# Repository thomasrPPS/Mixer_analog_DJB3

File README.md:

# Mixer_analog_DJB3

15 juin 2020 - 30 décembre 2020

Sommaire

Schema bloc, introduction
Tranche Phono/line
Autres éléments
PCB design
Montage
Démonstration
Sources

## Introduction

Voici le schéma du mixer V1 DJB3, pensé pour ressembler à un rotary mixer professionnel tel que la E&S DJR-400 ou la  Rane MP2015. 
Elle comprend 3 entrées Phono/Line pour tout type de signaux. De la platine vinyle aux drums machines et synthétiseurs. La première étape a été la modélisation 3d effectuée sur Blender
Chaque tranche est composée d’un equalizer 2 bandes grave/aigu sur les modèles de Baxandall.
Ensuite il y a un préamplificateur doté d’un switch selon la source entrante. Le coté phono se chargera d’appliquer la courbe RIAA et le gain est fixe (environ +40 dB à 20 Hz et +20 dB à 1 kHz). Le coté line sera doté d’un potentiomètre de gain à régler selon les besoins. 

Il y aura une carte amplificatrice BF en kit en sortie pour assurer la sommation et une puissance sonore convenable.
À celui ci sera relié un Vu mètre pour vérifier le niveau sonore en temps réel.

L’alimentation pour fournir le +12/-12v reste encore à déterminer lors de la phase de test pour connaitre la consommation réelle de l’appareil. Les tests devront s’effectuer avec une alimentation stabilisée réglable de laboratoire.

## Tranche phono/line

Nous allons détailler la composition de la tranche (encadré saumon du schéma bloc). Le schéma électronique est le suivant. C’est la partie du projet qui est à réaliser.

### Remarque
La courbe RIAA et donc le switch Phono/line devra être placé avant le correcteur de tonalité pour ne pas fausser la correction mais avant la résistance de sommation.

## PCB design

Le choix du type de mixer : modulaire
À partir du schéma, il faut choisir les bonnes empreintes correspondant aux composants préalablement achetés. Ensuite j’ai dessiné un premier schéma pas très concluant et pas très stratégique, après quelques révisions et modifications comme la largeur des pistes d’alimentation ainsi que la lecture plus logique du schéma on obtient le gerber présent dans le repository

## Montage

Entre temps je me suis rendu compte que j’avais fait une erreur dans le design du pcb et le potentiomètre qui règle l’égalisation des basses est à l’envers. Quelques heures de soudures et les soucis arrivent. Après avoir terminé les soudures sur la première tranche, je teste le son. Première bonne nouvelle, il y a du son ! Ensuite le gain en LINE fonctionne. Maintenant je branche un casque et là malheureusement je me rends compte que le son ne sort que d’un côté.
Je passe à la deuxième tranche qui marche en stéréo sans soucis puis à la 3e ou j’ai encore ce problème d’absence de son d’un côté, je soupçonne un problème de masse lié à mon alimentation ou aux connecteurs audio bas de gamme.
La partie montage pur débute avec la préparation d’une boite (à partir d’une plaque d’acier pliée avec une plieuse à zinc) et de trous pour les potentiomètres sur la face avant 

## Sources

https://www.sonelec-musique.com/electronique_realisations.html 

http://www.musicarius.com/blog/le-guide-dachat/le-guide-dachat-de-la-sono/le-guide-de-la-sonorisation/la-table-de-mixage 

http://users.otenet.gr/~athsam/2ch_mixer_eng.htm

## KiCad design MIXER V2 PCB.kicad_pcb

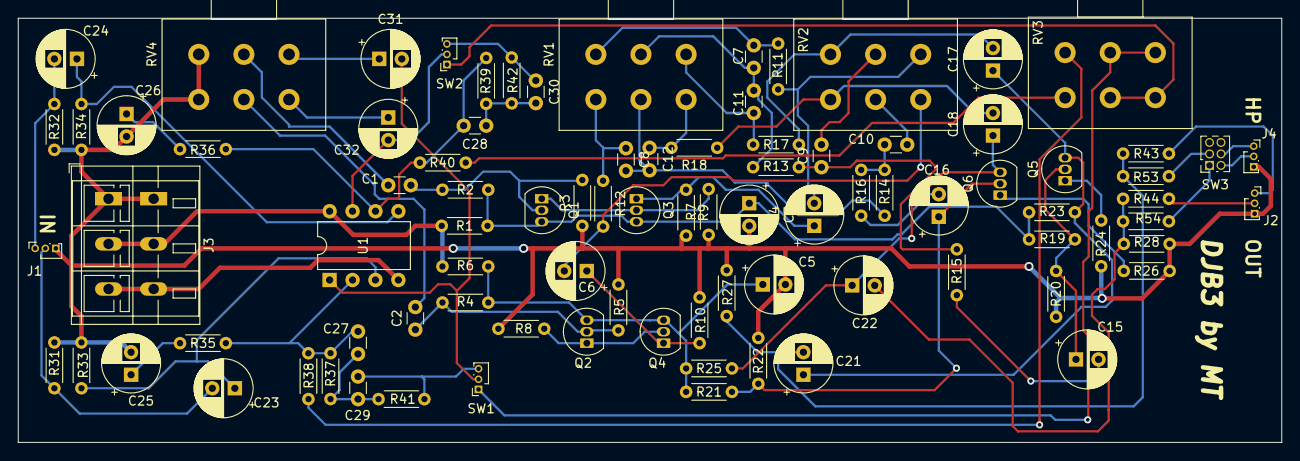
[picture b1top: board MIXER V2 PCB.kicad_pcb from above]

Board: 2 copper layers, 140.0 x 47.0 mm, 90 parts (0 on the bottom side), 63 nets.

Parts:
C1, C2, C7, C8, C11, C12: 100n; C_Disc_D3.0mm_W1.6mm_P2.50mm
C3, C5: 100u; CP_Radial_D6.3mm_P2.50mm
C4, C6, C15, C16, C21, C22: 22u; CP_Radial_D6.3mm_P2.50mm
C9, C10: 10n; C_Disc_D3.0mm_W1.6mm_P2.50mm
C17, C18: 4u7; CP_Radial_D6.3mm_P2.50mm
C23, C24: 220n; CP_Radial_D6.3mm_P2.50mm
C25, C26: 47u; CP_Radial_D6.3mm_P2.50mm
C27, C28: 750p; C_Disc_D3.0mm_W1.6mm_P2.50mm
C29, C30: 3n; C_Disc_D3.0mm_W1.6mm_P2.50mm
C31, C32: 10u; CP_Radial_D6.3mm_P2.50mm
J1, J2, J4: Conn_Coaxial_x2; PinSocket_1x03_P1.00mm_Vertical
J3: Conn_01x03; TerminalBlock_WAGO_236-403_1x03_P5.00mm_45Degree
Q1, Q2, Q3, Q4, Q5, Q6: BC107; TO-92_Inline
R1, R6: 100; R_Axial_DIN0204_L3.6mm_D1.6mm_P5.08mm_Horizontal
R2, R4, R19, R21, R37, R39: 100K; R_Axial_DIN0204_L3.6mm_D1.6mm_P5.08mm_Horizontal
R3, R5: 120K; R_Axial_DIN0204_L3.6mm_D1.6mm_P5.08mm_Horizontal
R7, R8, R20, R22: 12K; R_Axial_DIN0204_L3.6mm_D1.6mm_P5.08mm_Horizontal
R9, R10: 470; R_Axial_DIN0204_L3.6mm_D1.6mm_P5.08mm_Horizontal
R11, R12, R13, R14, R17, R18: 3K3; R_Axial_DIN0204_L3.6mm_D1.6mm_P5.08mm_Horizontal
R15, R16: 820; R_Axial_DIN0204_L3.6mm_D1.6mm_P5.08mm_Horizontal
R23, R25: 1K5; R_Axial_DIN0204_L3.6mm_D1.6mm_P5.08mm_Horizontal
R24, R26: 150; R_Axial_DIN0204_L3.6mm_D1.6mm_P5.08mm_Horizontal
R27, R28: 220K; R_Axial_DIN0204_L3.6mm_D1.6mm_P5.08mm_Horizontal
R31, R32: 47K; R_Axial_DIN0204_L3.6mm_D1.6mm_P5.08mm_Horizontal
R33, R34, R41, R42: 1M; R_Axial_DIN0204_L3.6mm_D1.6mm_P5.08mm_Horizontal
R35, R36: 1K2; R_Axial_DIN0204_L3.6mm_D1.6mm_P5.08mm_Horizontal
R38, R40: 10K; R_Axial_DIN0204_L3.6mm_D1.6mm_P5.08mm_Horizontal
R43, R44, R53, R54: 22K; R_Axial_DIN0204_L3.6mm_D1.6mm_P5.08mm_Horizontal
RV1, RV2, RV3, RV4: 100K; Potentiometer_Alps_RK163_Dual_Horizontal
SW1, SW2: LINE/PHONO; PinSocket_1x03_P1.00mm_Vertical
SW3: SW_DPST; PinSocket_2x03_P1.27mm_Vertical
U1: NE5532; DIP-8_W7.62mm

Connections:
+15V: J3.2, R1.2, R6.1, U1.8
-15V: J3.3, U1.4
GND: C3.2, C5.2, C25.2, C26.2, J1.3, J2.3, J3.1, J4.3, R3.1, R5.1, R7.1, R8.1, R9.2, R10.2, R20.2, R22.2, R24.2, R26.2, R27.2, R28.2, R31.2, R32.2, R33.2, R34.2, RV4.3, RV4.6
unnamed: C1.1, Q1.2, R2.1, R3.2
unnamed: C1.2, RV4.2
unnamed: C2.1, Q2.2, R4.1, R5.2
unnamed: C2.2, RV4.5
unnamed: C3.1, Q1.3, Q3.3, R1.1, R2.2, R19.1, R23.1
unnamed: C4.1, Q3.1, R9.1
unnamed: C4.2, R11.2, RV2.1
unnamed: C5.1, Q2.3, Q4.3, R4.2, R6.2, R21.1, R25.1
unnamed: C6.1, Q4.1, R10.1
unnamed: C6.2, R12.2, RV2.4
unnamed: C7.1, R11.1, RV1.3
unnamed: C8.1, R12.1, RV1.6
unnamed: C9.1, R13.1, R15.1
unnamed: C9.2, RV2.2
unnamed: C10.1, R14.1, R16.1
unnamed: C10.2, RV2.5
unnamed: C11.1, R17.2, RV1.1
unnamed: C7.2, C11.2, R13.2, RV1.2
unnamed: C12.1, R18.2, RV1.4
unnamed: C8.2, C12.2, R14.2, RV1.5
unnamed: C15.1, Q5.2, R19.2, R20.1
unnamed: C15.2, R15.2
unnamed: C16.1, Q6.2, R21.2, R22.1
unnamed: C16.2, R16.2
unnamed: C17.1, C21.1, Q5.3, R23.2
unnamed: C17.2, R17.1, RV2.3
unnamed: C18.1, C22.1, Q6.3, R25.2
unnamed: C18.2, R18.1, RV2.6
unnamed: C21.2, R27.1, R43.2, R53.2
unnamed: C22.2, R28.1, R44.2, R54.2
unnamed: C23.1, R33.1, U1.3
unnamed: C23.2, J1.2, R31.1
unnamed: C24.1, R34.1, U1.5
unnamed: C24.2, J1.1, R32.1
unnamed: C25.1, R35.2
unnamed: C26.1, R36.2
unnamed: C27.1, C29.2, R37.1, R41.2
unnamed: C27.2, R35.1, R37.2, R38.2, U1.2
unnamed: C28.1, C30.2, R39.2, R42.1
unnamed: C28.2, R36.1, R39.1, R40.1, U1.6
unnamed: C29.1, R41.1, SW1.3
unnamed: C30.1, R42.2, SW2.3
unnamed: C31.1, RV4.1
unnamed: C31.2, SW1.2, U1.1
unnamed: C32.1, RV4.4
unnamed: C32.2, SW2.2, U1.7
unnamed: J2.1, R43.1
unnamed: J2.2, R44.1
unnamed: J4.1, SW3.4
unnamed: J4.2, SW3.2
unnamed: Q1.1, Q3.2, R7.2
unnamed: Q2.1, Q4.2, R8.2
unnamed: Q5.1, R24.1
unnamed: Q6.1, R26.1
unnamed: R38.1, RV3.3
unnamed: R40.2, RV3.6
unnamed: R53.1, SW3.3
unnamed: R54.1, SW3.1
unnamed: RV3.1, RV3.2, SW1.1
unnamed: RV3.4, RV3.5, SW2.1

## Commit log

2022-02-16 documents & infos
2022-02-16 kicad project & gerber
